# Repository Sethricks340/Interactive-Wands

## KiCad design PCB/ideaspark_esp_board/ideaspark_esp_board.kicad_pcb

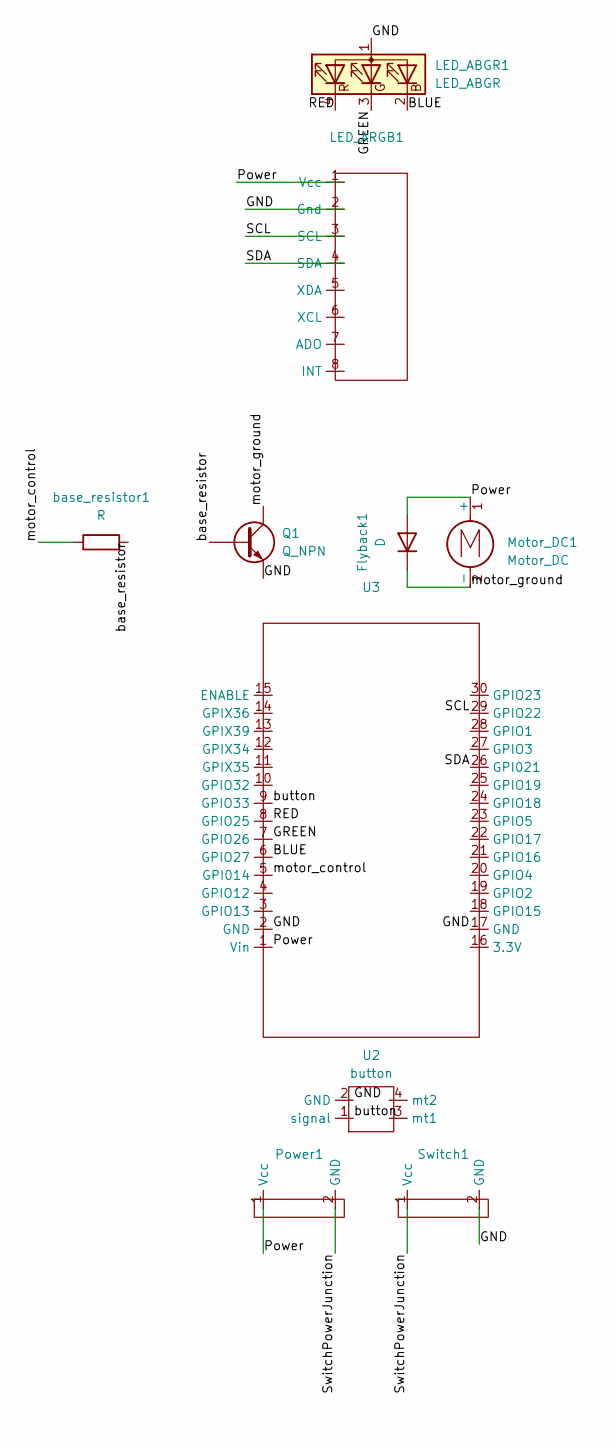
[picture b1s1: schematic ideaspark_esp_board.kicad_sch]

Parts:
Flyback1: D; two_through_holes_10.16
LED_ABGR1: LED_ABGR; rgb_led
LED_ARGB1: MPU_6050
Motor_DC1: Motor_DC; two_through_holes_10.16
Power1: two_through_holes_10.16
Q1: Q_NPN; Transistor
Switch1: two_through_holes_10.16
U2: button; Button
U3: ESP32_lcd_ideaspark
base_resistor1: R; two_through_holes_10.16

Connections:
/BLUE: LED_ABGR1.2 (BK), U3.6 (GPIO27)
/GND: LED_ABGR1.1 (A), LED_ARGB1.2 (Gnd), Q1.E, Switch1.2 (GND), U2.2 (GND), U3.2 (GND), U3.17 (GND)
/GREEN: LED_ABGR1.3 (GK), U3.7 (GPIO26)
/Power: Flyback1.2 (A), LED_ARGB1.1 (Vcc), Motor_DC1.1 (+), Power1.1 (Vcc), U3.1 (Vin)
/RED: LED_ABGR1.4 (RK), U3.8 (GPIO25)
/SCL: LED_ARGB1.3 (SCL), U3.29 (GPIO22)
/SDA: LED_ARGB1.4 (SDA), U3.26 (GPI021)
/SwitchPowerJunction: Power1.2 (GND), Switch1.1 (Vcc)
/base_resistor: Q1.B, base_resistor1.2
/button: U2.1 (signal), U3.9 (GPIO33)
/motor_control: U3.5 (GPI014), base_resistor1.1
/motor_ground: Flyback1.1 (K), Motor_DC1.2 (-), Q1.C

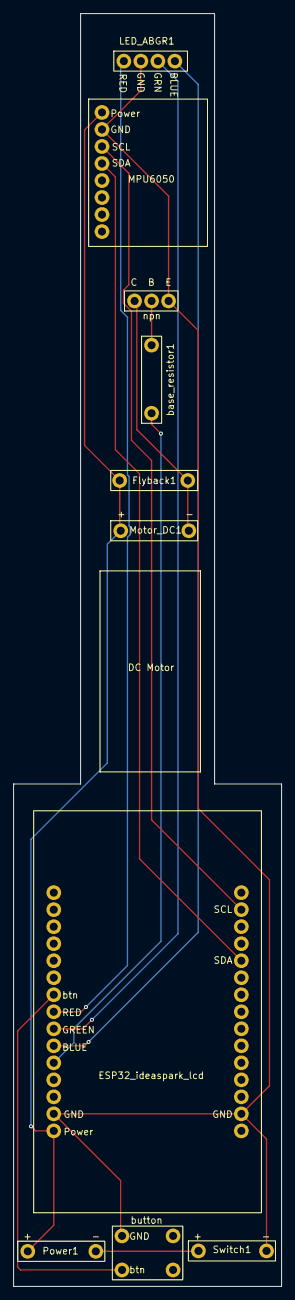
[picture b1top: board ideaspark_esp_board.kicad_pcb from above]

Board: 2 copper layers, 40.0 x 190.0 mm, 10 parts (0 on the bottom side), 12 nets.

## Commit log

2025-09-09 Initial commit - accelerometer works.
2025-09-09 Added timer ISR
2025-09-09 added bools for accel logic
2025-09-09 Added spell definitions and checking
2025-09-09 Changed timer ISR length
2025-09-09 Reverted to previous version, and deleted Gyro Calibration sequence.
2025-09-09 Only tracks first over threshold -> only one tracker per movement
2025-09-09 Added RBG colors to each spell, and a button to tell spell time frame.
2025-09-09 Added spell affects to spell struct
2025-09-09 Testing others affects
2025-09-10 Added character spells.
2025-09-10 added printing statements for debugging colors
2025-09-11 deleted lumos and nox
2025-09-24 started working with ESP w/LCD
2025-09-24 better balls bounce test
2025-09-24 balls collide
2025-09-24 updated the balls
2025-09-26 ESP can now send and recieve messages without a root node.
2025-09-27 Translated the arduino nano code to work with the ESP. ESP-NOW code is commented out for now.
2025-09-27 LCD now prints the name of the spell and other messages
2025-09-27 started working on the main screen layout
2025-09-28 added stun and shield icons
2025-09-28 made stun icon smaller
2025-09-28 arranged basic layotu of main screen.
2025-09-28 added clearing logic for the stun and shield areas
2025-09-28 preparing to merge lcd main screen to MPU file
2025-09-28 successfully merged LCD_main_main_screen to main wand logic.
2025-09-28 Deleted LCD_main_screen. Was merged.
2025-09-28 Added LED timeout after a spell is done.
2025-09-28 Implemented stunned logic.
2025-09-28 Fixed stun logic
2025-09-29 Wand with MPU6050 successfully sends data to other wands using ESP-NOW
2025-09-29 Confirmed that spells can be looped through to check on the reciever end. Added TODOs for next steps.
2025-09-29 others effects now in place
2025-09-30 changing things around to do points instead of lives
2025-09-30 Added skeleton code for base station
2025-09-30 Added more skeleton code.
2025-09-30 More skeleton code.
2025-10-01 started working on the start menu for the base station. Wands don't seem to be recieving the time esp now message
2025-10-01 revert to earlier version of esp now file
2025-10-01 added debug for printing incoming statments
2025-10-01 Removed debugging statement. Successfully sends out time every 10 seconds.
2025-10-01 Added waiting messages, and logic for recieving the first message from the base
2025-10-02 moved heavy logic out of ISR
2025-10-03 added clock symbol
2025-10-03 Wrote countdown timer in seconds
2025-10-03 added countdown timer in minutes:seconds
2025-10-03 added TODO for lives
2025-10-03 Created start game screen
2025-10-03 Created end game screen and logic
2025-10-03 centered base station timer
2025-10-03 update TODOs for later
2025-10-04 Deleted SpellResults struct, and replaced with using teh Spell struct. Haven't noticed any bugs with the change.
2025-10-05 Buzzer is now non-blocking, but can only do one buzz.
2025-10-05 Fixed start sequence bug
2025-10-05 Spells that have no effect on others aren’t broadcasted
2025-10-05 Created do hit spell function. untested.
2025-10-05 Added TODO
2025-10-05 Edited Spell effects, added notes for special spell effects
2025-10-05 Organized and renamed global scope elements
2025-10-06 Added special spell effects. Untested.
2025-10-16 fixed bug with receiving ESP rapidly triggering spell effects. Added flag clears in loop.
2025-10-16 changed hit color to red, along with if points is below zero.
2025-10-17 Added changing colors for the LED during waiting time.
2025-10-17 Changed invisibility cloak to expecto patronum
2025-10-17 Parameterized number of LEDs
2025-10-17 Update TODOs
2025-10-31 added working esp for reference to fix bugs
2025-11-02 wand receives signals from the base station from long distances, but wand-to-wand communication still isn't working well. Only works at short distances.
2025-11-09 Test Working Repo
    Test Working Repo
2025-11-11 PCB designs
    PCB designs
2025-11-12 Update ESP_NOW
    Update ESP_NOW
2025-11-13 Preparing for full test
    Preparing for a full test with all the wizards at once.
2025-11-13 Alohamora update
    Alohamora update
2025-11-14 Debugging and testing all wizards
    Debugging and testing all wizards
2025-11-14 Commented Out Character Spells
    Commented out character spells. Compiles, but untested. Will hopefully remove entirely if it works.
2025-11-14 Updated Spell list. added todo
2025-11-14 update todo
2025-11-15 Fine tuning with all wands
    Debugging all the wands.
2025-11-15 update todo
    update todo
2025-11-15 Fix Message Box Row
    The message box row works, but had to get rid of the colors.
2025-11-15 Changed ESP_NOW file name to wand_code
2025-11-16 Changed Spell Effects
    Changed Spell Effects
2025-11-16 Deleted Unused Variables and Irrelevant Comments
    Deleted Unused Variables and Irrelevant Comments
2025-11-19 Started Instruction Manual
    Started Instruction Manual
2025-11-20 Fixed Spell Checker Bug
    Wand was resetting after 4 moves. Fixed so that you can do any amount of moves, but after 4 is stops caring because none of the spells are that long.
2025-11-20 readRegisters bug?
    Testing to see if readRegisters is causing the random freeze.
2025-11-20 unblocked vibrator
2025-11-20 Changed 500 buzz to 250 buzz
    Changed 500 buzz to 250 buzz
2025-11-20 Define readRegisters
2025-11-20 Update TODOs
    Update TODOs
2025-11-20 Re-blocked buzz, started demo
    The buzzVibrator, which was blocking, is back. Also started a preliminary demo state.
2025-11-20 Finished Demo Mode
    Finished Demo Mod. There are no bugs so far.
2025-11-22 Change in_loop_ESP_recv
    Attempting to fix the freezing bug.
2025-11-22 Fix start message bug
2025-11-22 Update ISR
2025-11-22 Undo Last commit
2025-11-22 revert to previous commit
2025-11-22 Fix interrupt
    fixed no_interrupts so that start_sequence will work with delays
2025-11-26 Fixed led bug
2025-11-26 Motor control abstraction, untested
2025-11-29 Update Spells Dictionary
    Update Spells Dictionary
2025-11-30 Update Wand Dictionary
2025-11-30 Remove TODOs
2025-11-30 CAD Assembly
2025-12-05 Letter and Spell Printouts
2025-12-06 Explanation Video Script
2025-12-06 QR Code for the Video!!
2025-12-06 Video Thumbnail
2025-12-10 Might Make a YouTube Short
2025-12-10 More pictures for video
2025-12-11 YouTube short
